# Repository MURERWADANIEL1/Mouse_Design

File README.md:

# Mouse Design

This repository contains the electrical and mechanical design work for a compact 2.4 GHz wireless computer mouse. The focus of the project is on developing a **low‑noise, power‑efficient electrical subsystem** powered from a single‑cell 3.7 V 80 mAh LiPo battery with USB‑C charging.

## Project Objectives
This project aims to design a compact, low-noise, and power-efficient electrical subsystem for a 2.4 GHz wireless mouse powered by a 3.7 V 80 mAh LiPo battery with USB-C charging. The objective is to implement a reliable single-cell LiPo charging circuit with safe CC/CV operation, enable simultaneous operation while charging, and generate a clean, stable 3.3 V rail suitable for sensitive RF and digital circuitry. The design emphasizes low quiescent current for extended battery life, proper power domain isolation to minimize EMI and RF interference, robust input protection, and practical battery monitoring for system intelligence. The overall goal is to build a modular, production-ready power architecture that balances efficiency, simplicity, RF integrity, and reliability. The mechanical system of the mouse will be developed for the complete assembly.

1. **Battery management and charging** – implement a reliable single‑cell LiPo charging circuit supporting CC/CV operation and allowing the mouse to operate while charging. Ensure robust input protection and USB‑C compliance.
2. **Power conversion** – generate a clean, stable 3.3 V supply for RF and digital components. Emphasize low quiescent current to maximize standby and active battery life.
3. **EMI/RF integrity** – isolate power domains and minimize noise coupling between the RF transceiver, digital logic, and power circuitry.
4. **Protection and monitoring** – add over‑voltage, reverse‑polarity, and short‑circuit protection on the input, and include practical battery voltage/current monitoring for system intelligence and safety.
5. **Modularity and manufacturability** – build a production‑ready power architecture that balances efficiency, simplicity, and reliability within the constraints of a compact mouse form factor.
6. **Mechanical integration** – develop the mechanical system and enclosures so that the electrical subsystem and all components can be assembled into a finished mouse.

## Design Philosophy

- **Low noise**: Critical for the RF link and optical/laser sensor performance.
- **Low quiescent current**: Extend battery life to many weeks of normal use.
- **Safe and reliable**: Use established charging ICs and design practices to protect the cell and user.
- **Modular**: Separate power, RF, sensor, and mechanical domains to ease testing and future upgrades.

## Folder Structure

- `Project/` – design files, schematics, and BOMs.
- `MechanicalSystem Design/` – CAD files and mechanical assemblies.
- `Research Documents/` – datasheets, calculations, and reference material.

## Next Steps

Continue detailed schematic capture, PCB layout, and mechanical modelling. Validate power architecture on prototype boards, then iterate toward a production‑ready design.

---

*Last updated: February 26, 2026*

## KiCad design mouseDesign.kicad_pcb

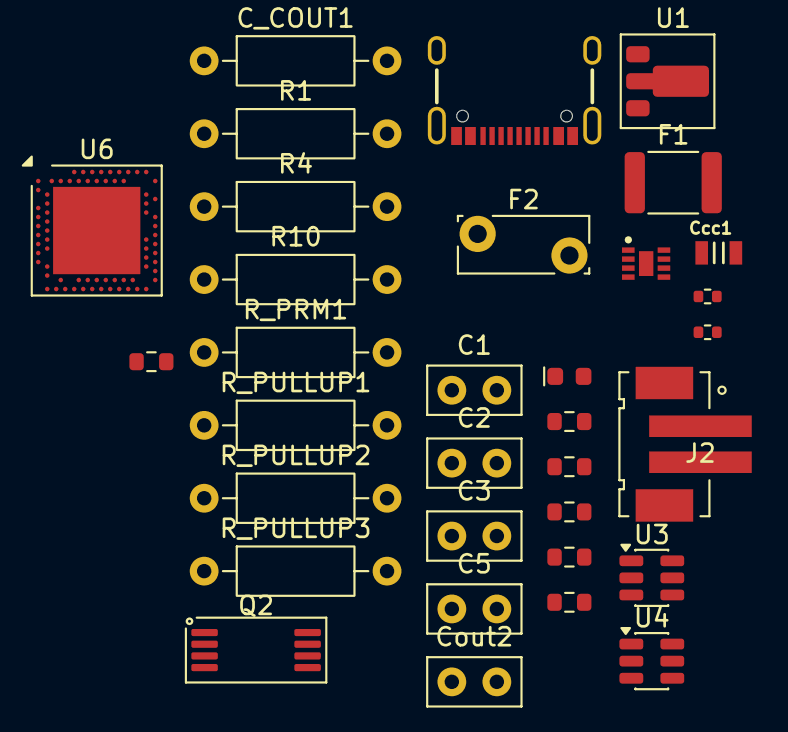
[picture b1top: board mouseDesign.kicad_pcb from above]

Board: 2 copper layers, 33 parts (0 on the bottom side), 27 nets, no tracks yet.

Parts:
C1: 10uF_Ceramic; C_Disc_D5.0mm_W2.5mm_P2.50mm
C2, C5: 100nF_Ceramic; C_Disc_D5.0mm_W2.5mm_P2.50mm
C3: 1nF_Ceramic; C_Disc_D5.0mm_W2.5mm_P2.50mm
C_COUT1: 1UF; R_Axial_DIN0207_L6.3mm_D2.5mm_P10.16mm_Horizontal
Ccc1: 0.1uF_0805_50V; C_0805
Cout2: 100nF_Ceramic; C_Disc_D5.0mm_W2.5mm_P2.50mm
D1: Green; LED_0603_1608Metric_Green
F1: Polyfuse; Fuse_1812_4532Metric
F2: Polyfuse; Fuse_Bourns_MF-RG300
J1: USB_C_Receptacle; USB-C_16
J2: JST_CONN; Header_JST_PH_1x02_P2mm_Vertical_SMD
Q2: AO8810; TSSOP-8_4.4x3mm_P0.65mm
R1: 1M; R_Axial_DIN0207_L6.3mm_D2.5mm_P10.16mm_Horizontal
R2, R3: 5.1k; R_0402_1005Metric
R4: Resistor; R_Axial_DIN0207_L6.3mm_D2.5mm_P10.16mm_Horizontal
R5: 4.7k; R_0603_1608Metric
R10: 100k; R_Axial_DIN0207_L6.3mm_D2.5mm_P10.16mm_Horizontal
R_CS1: 100; R_0603_1608Metric
R_ISET1: 36K; R_0603_1608Metric
R_LED1: 1k; R_0603_1608Metric
R_PRM1: 68K; R_Axial_DIN0207_L6.3mm_D2.5mm_P10.16mm_Horizontal
R_PULLUP1, R_PULLUP2: 4.7k; R_Axial_DIN0207_L6.3mm_D2.5mm_P10.16mm_Horizontal
R_PULLUP3: 100k; R_Axial_DIN0207_L6.3mm_D2.5mm_P10.16mm_Horizontal
R_TS1: 10k; R_0603_1608Metric
R_iSET2: 10k; R_0603_1608Metric
U1: MCP1700T-2502E-MB; SOT-89-3
U3: USBLC6-2SC6; SOT-23-6
U4: DW01A; SOT-23-6
U5: MAX17048; DFN-8_2x2mm_P0.5mm_EP1.2x0.8mm
U6: nRF52840; Nordic_AQFN-73-1EP_7x7mm_P0.5mm

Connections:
/3V3: Cout2.2, R_PULLUP1.2, R_PULLUP2.2, R_PULLUP3.2, U6.A22 (VDD), U6.AD14 (VDD), U6.AD23 (VDD), U6.B1 (VDD), U6.W1 (VDD), U6.Y2 (VDDH)
/DATA_N: U3.4 (I/O2), U6.AD4 (D-)
/DATA_P: U3.6 (I/O1), U6.AD6 (D+)
/INTRUPT_GPIO: R_PULLUP3.1, U5.5 (~ALRT)
/SCL: R_PULLUP2.1, U5.7 (SCL)
/SDA: R_PULLUP1.1, U5.8 (SDA)
/VUSB: R4.2, R10.1, U3.5 (VBUS), U6.AD2 (VBUS)
GND: C1.2, C2.1, C3.2, C5.1, C_COUT1.1 (+), Cout2.1, J1.GND, J2.2, Q2.6 (S2), Q2.7 (S2), R1.1, R2.2, R3.2, R5.1, R_ISET1.2, R_PRM1.2, R_iSET2.1, U1.1, U3.2 (GND), U4.6 (GND), U5.1 (CTG), U5.4 (GND), U5.6 (QSTRT), U5.9 (GND), U6.B7 (VSS), U6.EP (VSS)
unnamed: C1.1, F1.1
unnamed: C5.2, F2.2, R4.1
unnamed: R5.2, U6.AC5 (DECUSB)
unnamed: C_COUT1.2 (-), U1.3 (OUT)
unnamed: D1.2 (A), R_LED1.1
unnamed: F2.1, J1.VBUS
unnamed: J1.A5 (CC1), R2.1
unnamed: J1.B5 (CC2), R3.1
unnamed: J1.A6 (D+), J1.B6 (D+), U3.1 (I/O1)
unnamed: J1.A7 (D-), J1.B7 (D-), U3.3 (I/O2)
unnamed: C3.1, J1.S (SHIELD), R1.2
unnamed: Q2.1 (D), Q2.8 (D)
unnamed: Q2.4 (G1), U4.3 (OC)
unnamed: Q2.5 (G2), U4.1 (OD)
unnamed: Q2.2 (S1), Q2.3 (S1), R_CS1.1
unnamed: C2.2, U1.2 (IN)
unnamed: R_CS1.2, U4.2 (CS)
unnamed: Ccc1.2, U5.3 (VDD)
VBATT: Ccc1.1, F1.2, J2.1, R_LED1.2, R_TS1.2, U4.5 (VCC), U5.2 (CELL)

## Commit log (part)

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2026-02-26 Design Setup
2026-02-26 Updated documentation
